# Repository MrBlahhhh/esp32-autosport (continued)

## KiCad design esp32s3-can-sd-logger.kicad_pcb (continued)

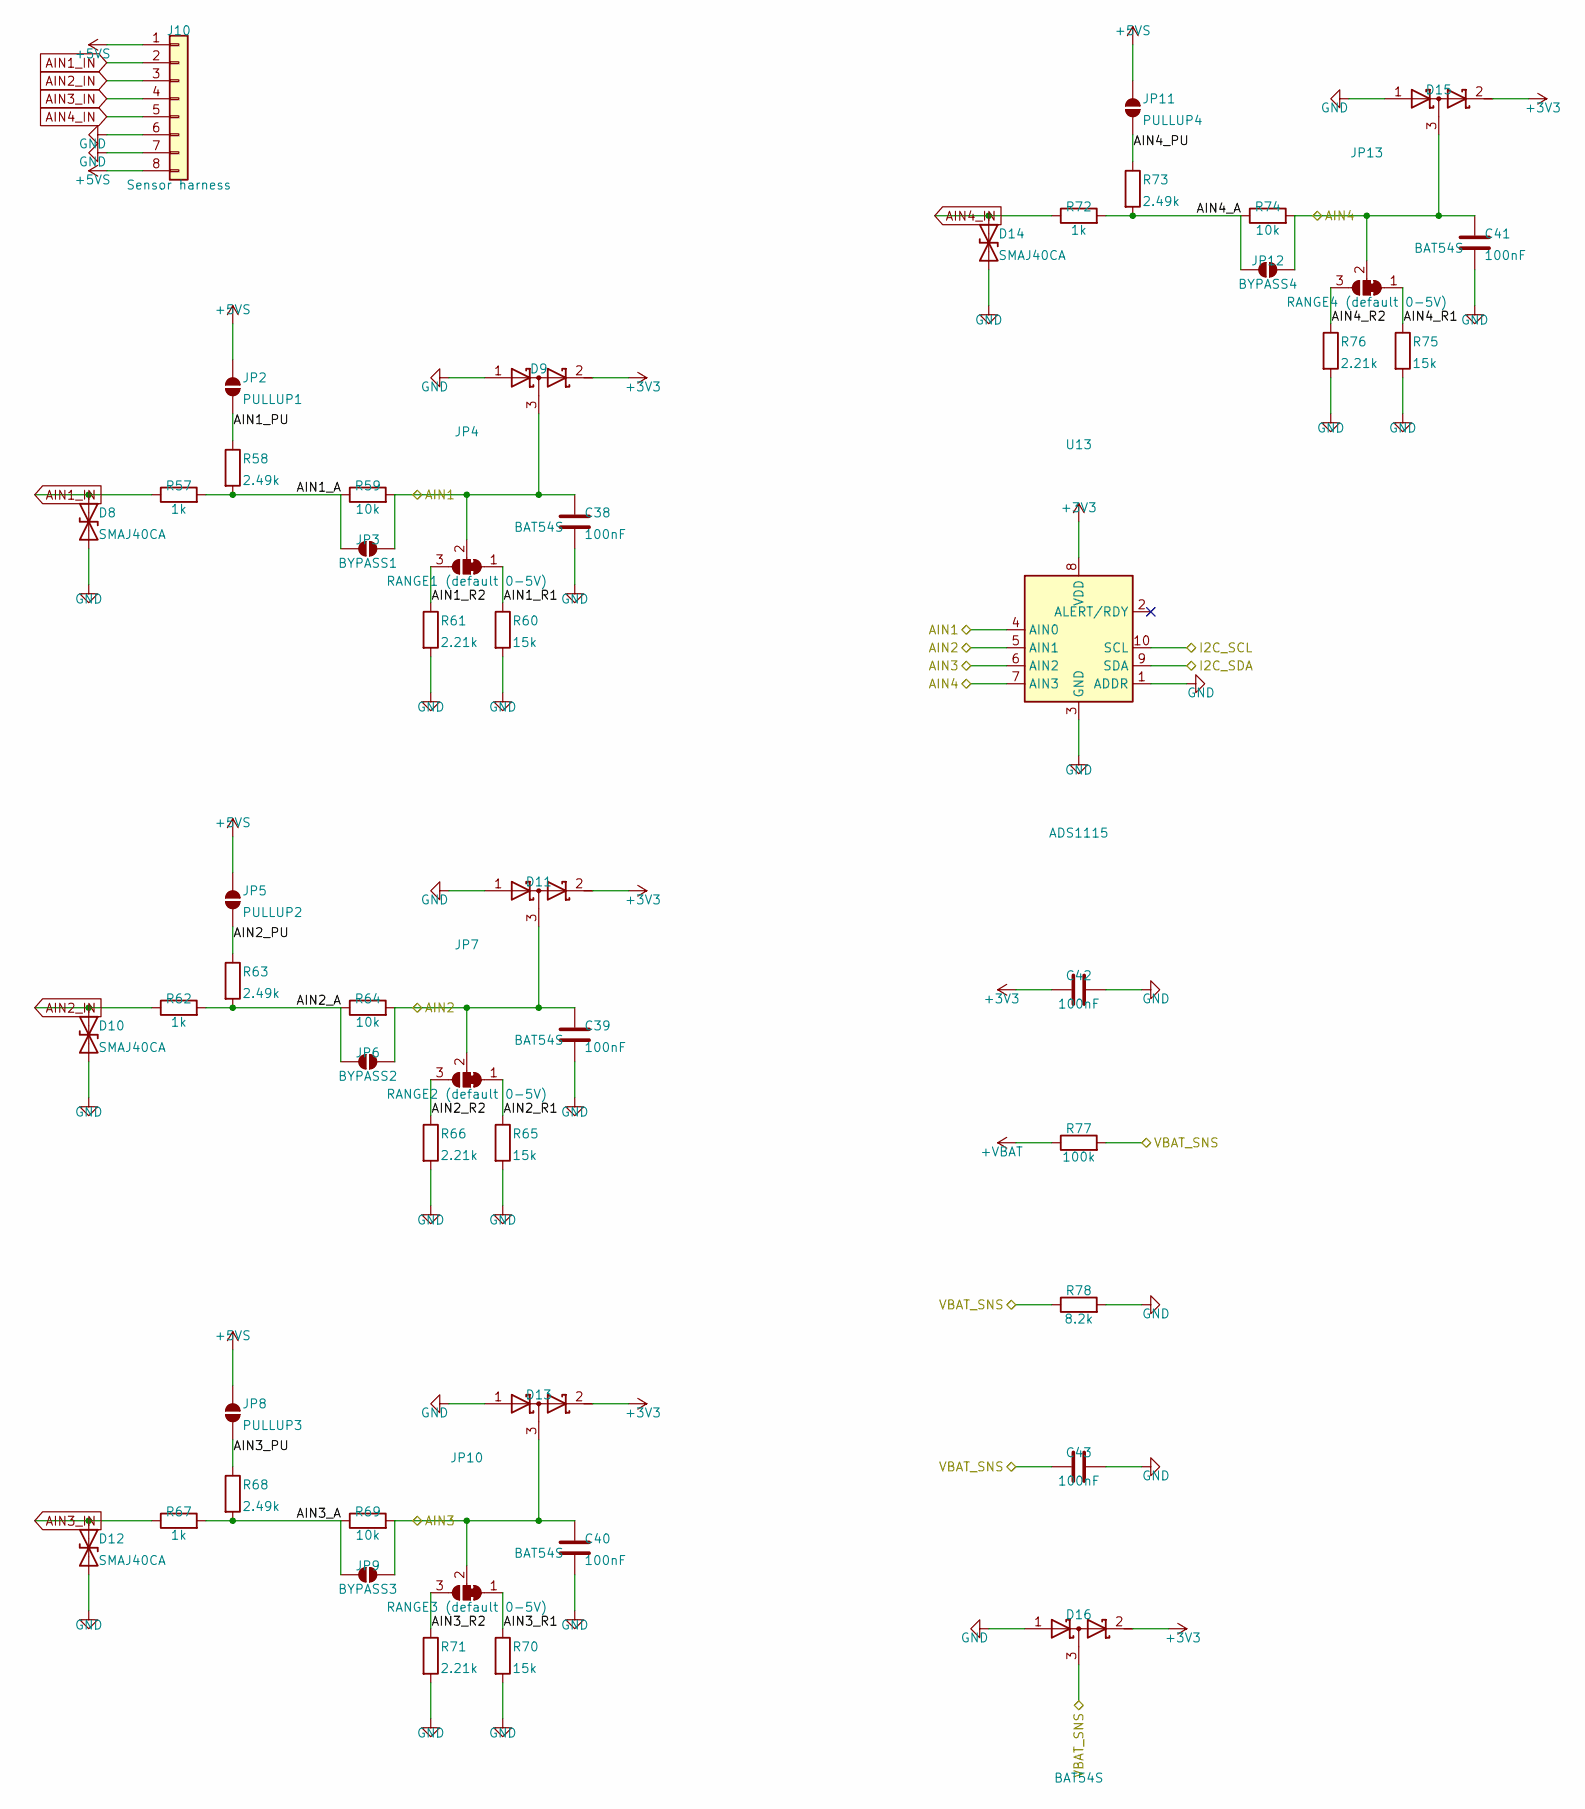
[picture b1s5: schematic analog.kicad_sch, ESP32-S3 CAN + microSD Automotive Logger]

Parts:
C38, C39, C40, C41, C42, C43: 100nF; C_0805_2012Metric; Voltage 16V
D8, D10, D12, D14: SMAJ40CA; D_SMA; MPN Littelfuse SMAJ40CA
D9, D11, D13, D15, D16: BAT54S; SOT-23; MPN MDD BAT54S
J10: Sensor harness; JST_PH_B8B-PH-K_1x08_P2.00mm_Vertical; MPN JST B8B-PH-K-S(LF)(SN)
JP2: PULLUP1; SolderJumper-2_P1.3mm_Open_Pad1.0x1.5mm
JP3: BYPASS1; SolderJumper-2_P1.3mm_Open_Pad1.0x1.5mm
JP4: RANGE1 (default 0-5V); SolderJumper-3_P1.3mm_Bridged12_Pad1.0x1.5mm
JP5: PULLUP2; SolderJumper-2_P1.3mm_Open_Pad1.0x1.5mm
JP6: BYPASS2; SolderJumper-2_P1.3mm_Open_Pad1.0x1.5mm
JP7: RANGE2 (default 0-5V); SolderJumper-3_P1.3mm_Bridged12_Pad1.0x1.5mm
JP8: PULLUP3; SolderJumper-2_P1.3mm_Open_Pad1.0x1.5mm
JP9: BYPASS3; SolderJumper-2_P1.3mm_Open_Pad1.0x1.5mm
JP10: RANGE3 (default 0-5V); SolderJumper-3_P1.3mm_Bridged12_Pad1.0x1.5mm
JP11: PULLUP4; SolderJumper-2_P1.3mm_Open_Pad1.0x1.5mm
JP12: BYPASS4; SolderJumper-2_P1.3mm_Open_Pad1.0x1.5mm
JP13: RANGE4 (default 0-5V); SolderJumper-3_P1.3mm_Bridged12_Pad1.0x1.5mm
R57, R62, R67, R72: 1k; R_0805_2012Metric; Tolerance 0.1%
R58, R63, R68, R73: 2.49k; R_0805_2012Metric
R59, R64, R69, R74: 10k; R_0805_2012Metric; Tolerance 0.1%
R60, R65, R70, R75: 15k; R_0805_2012Metric; Tolerance 0.1%
R61, R66, R71, R76: 2.21k; R_0805_2012Metric; Tolerance 0.1%
R77: 100k; R_0805_2012Metric
R78: 8.2k; R_0805_2012Metric
U13: ADS1115; VSSOP-10_3x3mm_P0.5mm; MPN ADS1115IDGSR

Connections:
+3V3: C42.1, D9.2 (K), D11.2 (K), D13.2 (K), D15.2 (K), D16.2 (K), U13.8 (VDD); also elsewhere on the board
+5VS: J10.1, J10.8, JP2.1 (A), JP5.1 (A), JP8.1 (A), JP11.1 (A); also elsewhere on the board
+VBAT: R77.1; also elsewhere on the board
AIN1: C38.1, D9.3 (common), JP3.2 (B), JP4.2 (C), R59.2, U13.4 (AIN0); also elsewhere on the board
AIN1_A: JP3.1 (A), R57.2, R58.2, R59.1
AIN1_IN: D8.1 (A1), J10.2, R57.1
AIN1_PU: JP2.2 (B), R58.1
AIN1_R1: JP4.1 (A), R60.1
AIN1_R2: JP4.3 (B), R61.1
AIN2: C39.1, D11.3 (common), JP6.2 (B), JP7.2 (C), R64.2, U13.5 (AIN1); also elsewhere on the board
AIN2_A: JP6.1 (A), R62.2, R63.2, R64.1
AIN2_IN: D10.1 (A1), J10.3, R62.1
AIN2_PU: JP5.2 (B), R63.1
AIN2_R1: JP7.1 (A), R65.1
AIN2_R2: JP7.3 (B), R66.1
AIN3: C40.1, D13.3 (common), JP9.2 (B), JP10.2 (C), R69.2, U13.6 (AIN2); also elsewhere on the board
AIN3_A: JP9.1 (A), R67.2, R68.2, R69.1
AIN3_IN: D12.1 (A1), J10.4, R67.1
AIN3_PU: JP8.2 (B), R68.1
AIN3_R1: JP10.1 (A), R70.1
AIN3_R2: JP10.3 (B), R71.1
AIN4: C41.1, D15.3 (common), JP12.2 (B), JP13.2 (C), R74.2, U13.7 (AIN3); also elsewhere on the board
AIN4_A: JP12.1 (A), R72.2, R73.2, R74.1
AIN4_IN: D14.1 (A1), J10.5, R72.1
AIN4_PU: JP11.2 (B), R73.1
AIN4_R1: JP13.1 (A), R75.1
AIN4_R2: JP13.3 (B), R76.1
I2C_SCL: U13.10 (SCL); also elsewhere on the board
I2C_SDA: U13.9 (SDA); also elsewhere on the board
VBAT_SNS: C43.1, D16.3 (common), R77.2, R78.1; also elsewhere on the board

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
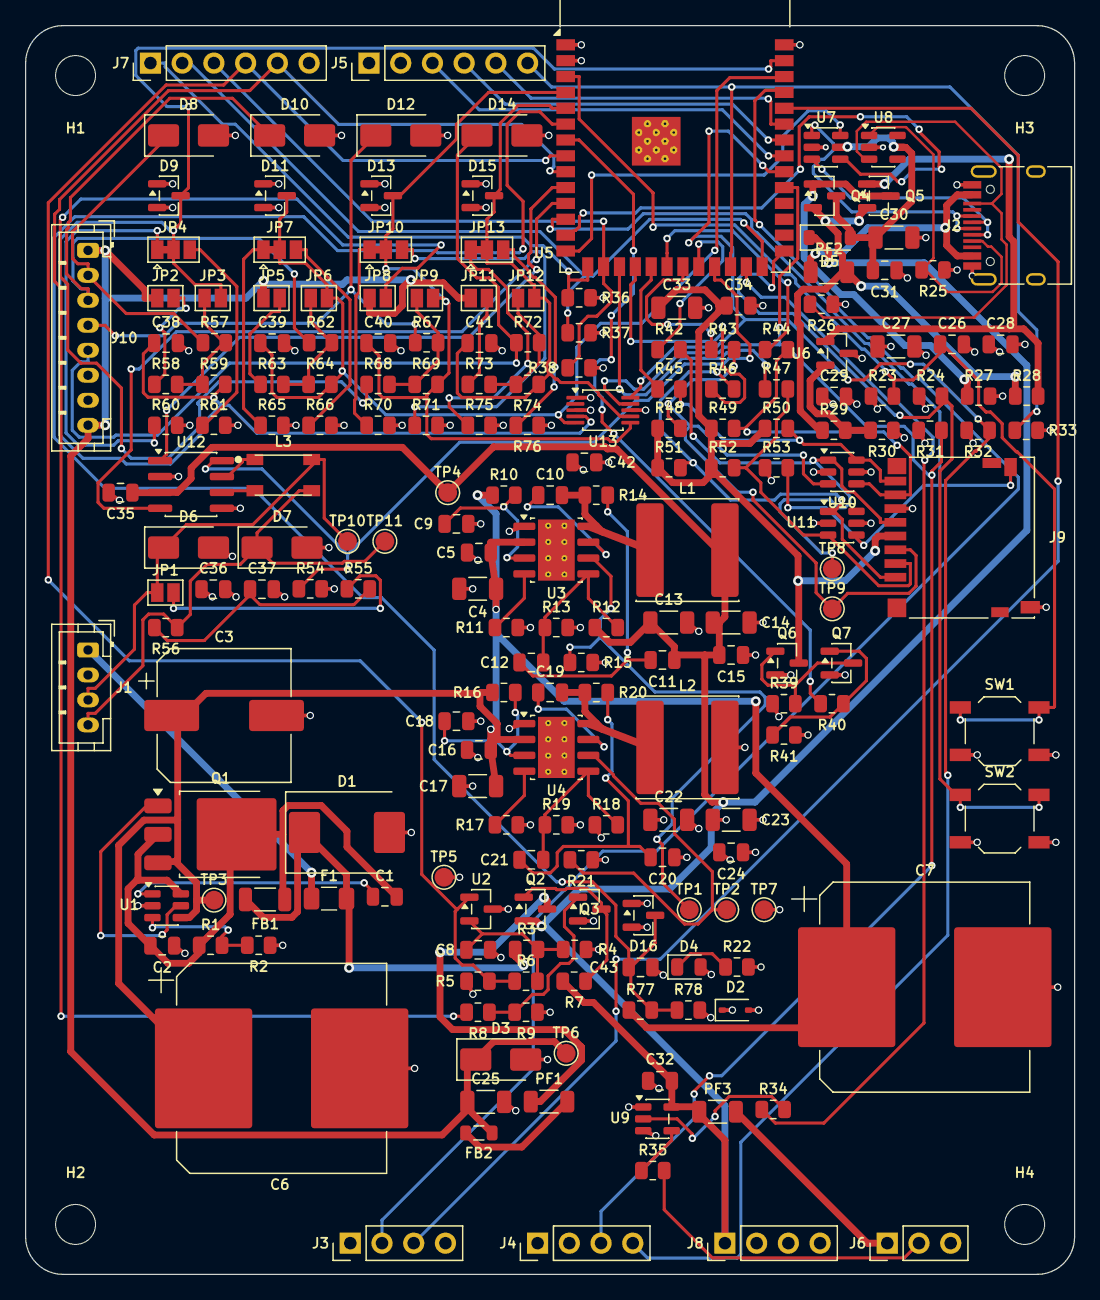
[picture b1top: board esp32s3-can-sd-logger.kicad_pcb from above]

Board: 4 copper layers, 84.0 x 100.0 mm, 206 parts (0 on the bottom side), 114 nets.

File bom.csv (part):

Qty (1 board),Qty (10 boards),References,Value,Voltage,Tolerance,Footprint,Manufacturer part number,LCSC,Notes
1,10,C1,1uF,50V,,Capacitor_SMD:C_0805_2012Metric,,,LM74700 charge-pump reservoir
4,40,C10 C11 C19 C20,2.2nF,50V,,Capacitor_SMD:C_0805_2012Metric,,,Bootstrap: datasheet mandates exactly 2.2nF X7R -- a larger value overstresses the internal VCC regulator and damages the device
2,20,C12 C21,270pF,50V,,Capacitor_SMD:C_0805_2012Metric,,,Ramp coupling capacitor CB
4,40,C13 C14 C22 C23,22uF,16V,,Capacitor_SMD:C_1206_3216Metric,,,
15,150,C15 C24 C28 C29 C31 C32 C34 C35 C36 C38 C39 C40 C41 C42 C43,100nF,16V,,Capacitor_SMD:C_0805_2012Metric,,,
3,30,C16 C2 C5,100nF,100V,,Capacitor_SMD:C_0805_2012Metric,,,LM74700 ANODE input capacitor: the datasheet requires a minimum 22nF at ANODE and this node is behind FB1 with nothing else on it
4,40,C25 C27 C30 C33,10uF,16V,,Capacitor_SMD:C_1206_3216Metric,,,
1,10,C26,1uF,16V,,Capacitor_SMD:C_0805_2012Metric,,,EN reset delay
1,10,C3,100uF,100V,,Capacitor_SMD:CP_Elec_10x10.5,Nichicon UCD2A101MNL1GS,,Bulk hold-up; any 100uF >=80V SMD electrolytic on a 10x10.5 land works -- match in the JLC catalog at order. Pin 1 is +
1,10,C37,4.7nF,50V,,Capacitor_SMD:C_0805_2012Metric,,,Split-termination common-mode stabiliser
2,20,C17 C4,10uF,100V,,Capacitor_SMD:C_1206_3216Metric,,,Switcher input bypass
2,20,C6 C7,330uF,100V,,Capacitor_SMD:CP_Elec_16x22,,,"Power-fail ride-through. With the sensor rail shed and the LEDs off the board draws about 0.35 W here, so the bank holds the rails up long enough to finish the block in flight and close the file. 16x22 rather than 16x17.5: the two footprints are identical in every copper and courtyard layer -- only the can is 4.5 mm taller -- so the extra 220 uF costs nothing but enclosure height. Any 330uF >=80V on a 16 mm land works; match in the JLC catalogue at order. Pin 1 is +"
1,10,C8,1nF,50V,,Capacitor_SMD:C_0805_2012Metric,,,Just enough to keep switching noise off the reference. Larger would delay the very detection this exists to make early
2,20,C18 C9,10nF,100V,,Capacitor_SMD:C_0805_2012Metric,,,EN sits on a bare 100k to VBAT; this keeps a high-impedance enable node quiet in a vehicle
1,10,D1,SMCJ40CA,,,Diode_SMD:D_SMC,Littelfuse SMCJ40CA,C80273,"40V standoff / 64.5V clamp @ 1500W, bidirectional: absorbs ISO 7637-2 pulse 5b load dump and the negative pulses, ahead of the FET. 40V not 33V so the part stands off the declared 36V input top"
1,10,D2,3.6V 300mW,,,Diode_SMD:D_SOD-323,onsemi MM3Z3V6T1G,C116949,Rail clamp: an analog input shorted to battery back-feeds ~1.6mA through its BAT54S into +3V3; with the MCU asleep the rail would otherwise float above the ESP32's 3.6V absolute maximum
1,10,D3,SMAJ6.0A,,,Diode_SMD:D_SMA,Littelfuse SMAJ6.0A,C223993,"Clamps harness-injected transients on the sensor 5V. 6.0V standoff, not 5.0V: a 5.0V part on a 5.0V rail leaks up to 800uA continuously"
1,10,D4,green,,,LED_SMD:LED_0805_2012Metric,,,"The board's only LED: +3V3 is up, so the whole supply chain came through -- battery, ideal diode, and both converters"
1,10,D5,40V 1A,,,Diode_SMD:D_SOD-123,PMEG4010,,"OR-ing: bench USB can power the board, but the 5V buck (5.00V) reverse-biases it whenever the car is connected"
2,20,D6 D7,SMAJ26CA,,,Diode_SMD:D_SMA,Diodes Inc SMAJ26CA-13-F,C134976,Bidirectional bus clamp
4,40,D10 D12 D14 D8,SMAJ40CA,,,Diode_SMD:D_SMA,Littelfuse SMAJ40CA,C223989,"Ch1 harness transient clamp (bidirectional, 400W)"
5,50,D11 D13 D15 D16 D9,BAT54S,,,Package_TO_SOT_SMD:SOT-23,MDD BAT54S,C408389,Ch1 rail clamp (both polarities)
1,10,F1,2A slow,,,Fuse:Fuse_1206_3216Metric,Littelfuse 0466002.NR,,"Sacrificial: only opens on a hard fault, not on reverse polarity"
1,10,FB1,600R,,,Inductor_SMD:L_1206_3216Metric,Wurth 742792625,,Conducted-emissions bead
1,10,FB2,600R,,,Inductor_SMD:L_0805_2012Metric,Wurth 742792022,,
4,40,H1 H2 H3 H4,M3,,,MountingHole:MountingHole_3.2mm_M3,,,
1,10,J1,PWR + CAN harness,,,Connector_JST:JST_PH_B4B-PH-K_1x04_P2.00mm_Vertical,JST B4B-PH-K-S(LF)(SN),C131334,"Pin 1 +12V, 2 GND, 3 CAN_H, 4 CAN_L (Autosport Labs harness order)"
1,10,J10,Sensor harness,,,Connector_JST:JST_PH_B8B-PH-K_1x08_P2.00mm_Vertical,JST B8B-PH-K-S(LF)(SN),C157974,Two 5V and two ground pins so sensors can be paired up
1,10,J2,USB-C,,,Connector_USB:USB_C_Receptacle_HRO_TYPE-C-31-M-12,HRO TYPE-C-31-M-12,C165948,Programming / CDC console only -- not a power path in the car
1,10,J3,UART0,,,Connector_PinHeader_2.54mm:PinHeader_1x04_P2.54mm_Vertical,,,
1,10,J4,I2C / Qwiic,,,Connector_PinHeader_2.54mm:PinHeader_1x04_P2.54mm_Vertical,,,
1,10,J5,SPI,,,Connector_PinHeader_2.54mm:PinHeader_1x06_P2.54mm_Vertical,,,IO40 SCK / IO41 MISO / IO42 MOSI / IO47 CS -- GPIO-matrix SPI
1,10,J6,WS2812,,,Connector_PinHeader_2.54mm:PinHeader_1x03_P2.54mm_Vertical,,,Shift-light header: +5V / 5V-logic DIN / GND
1,10,J7,Spare IO,,,Connector_PinHeader_2.54mm:PinHeader_1x06_P2.54mm_Vertical,,,"IO3/IO45/IO46 are strapping pins, each with a 10k pull-down -- anything attached must not fight them at boot. Pins 4 and 5 are no longer spare: IO15 is the power-fail interrupt and IO16 is the sensor-rail enable. They stay on the header as probe points, so the ride-through can be watched on a scope without unsoldering anything, but nothing else may drive them. The ground pin is here so a probe or a ribbon has a return"
1,10,J8,Rail break-out,,,Connector_PinHeader_2.54mm:PinHeader_1x04_P2.54mm_Vertical,,,
1,10,J9,microSD push-pull,,,Connector_Card:microSD_HC_Hirose_DM3D-SF,Hirose DM3D-SF,C719027,Push-pull socket; DET is the card-present switch
1,10,JP1,TERM (default OFF),,,Jumper:SolderJumper-2_P1.3mm_Open_Pad1.0x1.5mm,,,"Ships OPEN: unterminated. Bridge the pads only when this board is an END node on its own bus. A vehicle's bus -- OBD-II diagnostics included -- is already terminated at both ends, and a third 120 ohm across the pair takes it to about 40 ohm and can stop it working. Defaulting terminated made that an easy mistake to make"
1,10,JP10,RANGE3 (default 0-5V),,,Jumper:SolderJumper-3_P1.3mm_Bridged12_Pad1.0x1.5mm,,,"Ships BRIDGED 1-2 = the 0-5V range, which is what almost every automotive sensor is. Cut 1-2 and bridge 2-3 for 0-16V; cut 1-2 and leave both open for no divider (then close BYPASS3 for a raw 0-3.3V sensor). Defaulting to 0-5V also means the firmware's DIVIDER_GAIN matches the board as shipped"
1,10,JP11,PULLUP4,,,Jumper:SolderJumper-2_P1.3mm_Open_Pad1.0x1.5mm,,,Close for 2-wire NTC / open-collector sensors
1,10,JP12,BYPASS4,,,Jumper:SolderJumper-2_P1.3mm_Open_Pad1.0x1.5mm,,,Close for a raw 0-3.3V sensor (shorts the upper leg)
1,10,JP13,RANGE4 (default 0-5V),,,Jumper:SolderJumper-3_P1.3mm_Bridged12_Pad1.0x1.5mm,,,"Ships BRIDGED 1-2 = the 0-5V range, which is what almost every automotive sensor is. Cut 1-2 and bridge 2-3 for 0-16V; cut 1-2 and leave both open for no divider (then close BYPASS4 for a raw 0-3.3V sensor). Defaulting to 0-5V also means the firmware's DIVIDER_GAIN matches the board as shipped"
1,10,JP2,PULLUP1,,,Jumper:SolderJumper-2_P1.3mm_Open_Pad1.0x1.5mm,,,Close for 2-wire NTC / open-collector sensors
1,10,JP3,BYPASS1,,,Jumper:SolderJumper-2_P1.3mm_Open_Pad1.0x1.5mm,,,Close for a raw 0-3.3V sensor (shorts the upper leg)
1,10,JP4,RANGE1 (default 0-5V),,,Jumper:SolderJumper-3_P1.3mm_Bridged12_Pad1.0x1.5mm,,,"Ships BRIDGED 1-2 = the 0-5V range, which is what almost every automotive sensor is. Cut 1-2 and bridge 2-3 for 0-16V; cut 1-2 and leave both open for no divider (then close BYPASS1 for a raw 0-3.3V sensor). Defaulting to 0-5V also means the firmware's DIVIDER_GAIN matches the board as shipped"
1,10,JP5,PULLUP2,,,Jumper:SolderJumper-2_P1.3mm_Open_Pad1.0x1.5mm,,,Close for 2-wire NTC / open-collector sensors
1,10,JP6,BYPASS2,,,Jumper:SolderJumper-2_P1.3mm_Open_Pad1.0x1.5mm,,,Close for a raw 0-3.3V sensor (shorts the upper leg)
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
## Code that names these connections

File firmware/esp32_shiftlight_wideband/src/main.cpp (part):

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#define LED_TYPE    WS2812B
#define COLOR_ORDER GRB

#define CAN_TX_PIN  GPIO_NUM_17
#define CAN_RX_PIN  GPIO_NUM_18
#define CAN_S_PIN   21            // low = normal, high = listen-only

#define PWR_FAIL_PIN 15           // rising = harness below 11 V
#define SENS_EN_PIN  16           // high = +5VS live; off at reset
#define SD_PWR_EN_PIN 7
#define SD_CD_PIN     8
#define SD_CLK_PIN 14
#define SD_CMD_PIN 13
#define SD_D0_PIN  12
#define SD_D1_PIN  11
#define SD_D2_PIN  10
#define SD_D3_PIN   9

#define RPM_STALE_MS 2000         // blank the strip if CAN goes quiet

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// of the R53 board's 10k/10k, and using it here reads 17 % high all the way up
// the range. gen/simulate_firmware.py study 3 measures it end to end.
static const float DIVIDER_GAIN = 1.7334f;
static const int   ESP_ADC_PIN  = 1;       // AIN1 = GPIO1 = ADC1_CH0
static const int   VBAT_ADC_PIN = 6;       // VBAT_SNS = GPIO6, divided by 11
static const float VBAT_DIVIDER = 11.0f;

// I2C is on the Qwiic header, not the pins the R53 board used — GPIO7 and
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
void IRAM_ATTR onPowerFail() {
  powerFailed = true;
  digitalWrite(SENS_EN_PIN, LOW);
}

/**
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  // CAN_S low = normal mode. R40 already pulls it there so the transceiver is
  // sane while the MCU is in reset; drive it anyway so the state is the
  // firmware's decision and not a resistor's.
  pinMode(CAN_S_PIN, OUTPUT);
  digitalWrite(CAN_S_PIN, LOW);

  twai_general_config_t g =
      TWAI_GENERAL_CONFIG_DEFAULT(CAN_TX_PIN, CAN_RX_PIN, TWAI_MODE_NORMAL);
  g.rx_queue_len = 32;   // FastLED.show() blocks ~0.5 ms; don't drop frames in it
  twai_timing_config_t t = TWAI_TIMING_CONFIG_500KBITS();
  twai_filter_config_t f = TWAI_FILTER_CONFIG_ACCEPT_ALL();
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
// --- microSD -----------------------------------------------------------------
void sdInit() {
  pinMode(SD_CD_PIN, INPUT);
  pinMode(SD_PWR_EN_PIN, OUTPUT);
  digitalWrite(SD_PWR_EN_PIN, HIGH);       // the card supply is switched
  delay(10);                               // let the rail come up before clocking

  SD_MMC.setPins(SD_CLK_PIN, SD_CMD_PIN, SD_D0_PIN, SD_D1_PIN, SD_D2_PIN, SD_D3_PIN);
  if (!SD_MMC.begin("/sdcard", false)) {   // 4-bit: ~4x the write throughput
    Serial.println("SD: mount failed");
    return;
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
/**
 * The firmware half of README section 2. The hardware guarantees roughly
 * 108 ms between PWR_FAIL and the converters dropping out; this is what spends
 * it. Order matters: the sensor rail is already off (the ISR did it), the strip
 * goes dark so it is not drawing from the bank, then the file is closed, and
 * only then is the card supply removed — with SD_MMC.end() first, because
 * dropping SD_PWR_EN while the bus pins are still driven back-feeds the card
 * through its ESD structures (README section 5).
 */
void shutdown() {
  if (shuttingDown) return;
  shuttingDown = true;
  digitalWrite(SENS_EN_PIN, LOW);          // idempotent; the ISR got here first

  FastLED.clear(true);

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    SD_MMC.end();
    sdUp = false;
  }
  digitalWrite(SD_PWR_EN_PIN, LOW);

  Serial.printf("PWR_FAIL at %lu ms: %lu lines flushed and closed\n", millis(), logLines);
}
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  // +5VS is off at reset by design: it is an external load firmware must be
  // able to shed. Nothing on the sensor harness reads anything until this
  // goes high, and every analog reading before it is a zero.
  pinMode(SENS_EN_PIN, OUTPUT);
  digitalWrite(SENS_EN_PIN, HIGH);

  // Armed before anything slow runs. An ignition cut during BLE bring-up is
  // still an ignition cut, and the card is not open yet but the interrupt
  // still has to be the thing that shuts the rail down.
  pinMode(PWR_FAIL_PIN, INPUT);
  attachInterrupt(digitalPinToInterrupt(PWR_FAIL_PIN), onPowerFail, RISING);

  // BLE goes first, on purpose. The BT controller wants a sizeable block of
  // internal RAM (it cannot use PSRAM) and it is the one subsystem here that
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
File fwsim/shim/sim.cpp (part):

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    fault(SEV_ERROR, "PIN_PSRAM", "GPIO%d driven, but it is octal PSRAM on this module", gpio);
  if (p && p->role == ROLE_SD_PWR_EN && level == 0 && s.sd_begun)
    fault(SEV_WARN, "SD_BACKFEED",
          "SD_PWR_EN (GPIO%d) dropped while the card is still mounted. Call SD_MMC.end() first, "
          "or the MCU keeps driving the bus into an unpowered card through its ESD structures "
          "(README section 5)",
          gpio);
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    int en = gpio_with_role(ROLE_SENS_EN);
    fault(SEV_ERROR, "SENSOR_RAIL_OFF",
          "channel %d (GPIO%d) is excited from +5VS, which is off at reset -- firmware never drove "
          "SENS_EN (GPIO%d) high, so this channel reads 0 V no matter what the sensor does",
          ch, gpio, en);
    src = 0.0;
  }
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  s.can_pins_ok = true;
  if (want_tx >= 0 && tx != want_tx) {
    const PinDef* p = find_pin(tx);
    fault(SEV_ERROR, "CAN_TX_PIN",
          "TWAI TX assigned to GPIO%d (%s), but this board wires the transceiver TXD to GPIO%d -- "
          "no frames will ever arrive, and GPIO%d is now driven by the CAN controller",
          tx, p ? role_name(p->role) : "not connected", want_tx, tx);
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  }
  if (want_rx >= 0 && rx != want_rx) {
    const PinDef* p = find_pin(rx);
    fault(SEV_ERROR, "CAN_RX_PIN",
          "TWAI RX assigned to GPIO%d (%s), but this board wires the transceiver RXD to GPIO%d",
          rx, p ? role_name(p->role) : "not connected", want_rx, rx);
    s.can_pins_ok = false;
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  int cs = gpio_with_role(ROLE_CAN_S);
  if (cs >= 0 && !pin_driven(cs))
    fault(SEV_NOTE, "CAN_S_DEFAULT",
          "CAN_S (GPIO%d) left undriven; R54 pulls it low so the transceiver comes up in normal "
          "mode. Drive it high for listen-only if this node must never ACK",
          cs);
}
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  s.i2c_pins_ok = true;
  if (want_sda >= 0 && sda != want_sda) {
    const PinDef* p = find_pin(sda);
    fault(SEV_ERROR, "I2C_SDA_PIN",
          "I2C SDA brought up on GPIO%d, but on this board GPIO%d is %s (%s) and the bus is on "
          "GPIO%d. Driving it toggles that function",
          sda, sda, p ? p->net : "nothing", p ? role_name(p->role) : "not connected", want_sda);
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  }
  if (want_scl >= 0 && scl != want_scl) {
    const PinDef* p = find_pin(scl);
    fault(SEV_ERROR, "I2C_SCL_PIN",
          "I2C SCL brought up on GPIO%d, but on this board GPIO%d is %s (%s) and the bus is on "
          "GPIO%d",
          scl, scl, p ? p->net : "nothing", p ? role_name(p->role) : "not connected", want_scl);
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  int pwr = gpio_with_role(ROLE_SD_PWR_EN);
  if (pwr >= 0 && !(s.level.count(pwr) && s.level[pwr] == 1)) {
    fault(SEV_ERROR, "SD_UNPOWERED",
          "SD_MMC.begin() with SD_PWR_EN (GPIO%d) low -- the card supply is switched through "
          "Q2/Q3 and off at reset, so there is no card on the bus to answer",
          pwr);
    return false;
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  s.stop_reason = why ? why : "";
  if (s.pwr_fail_at_ms >= 0.0 && !s.pwr_fail_observed)
    fault(SEV_ERROR, "PWR_FAIL_IGNORED",
          "PWR_FAIL (GPIO%d) asserted at %.1f ms and firmware never read it or attached an "
          "interrupt to it. The hardware buys a %.0f ms window to shed the sensor rail and close "
          "the file; nothing in this firmware spends it",
          gpio_with_role(ROLE_PWR_FAIL), s.pwr_fail_at_ms, board().ridethru_shed_ms);
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
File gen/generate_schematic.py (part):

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
part(pw, "J", "Connector_Generic:Conn_01x04", "PWR + CAN harness", JST4,
     {"1": "VBAT_IN", "2": "GND", "3": "CAN_H", "4": "CAN_L"},
     "JST B4B-PH-K-S(LF)(SN)", "Pin 1 +12V, 2 GND, 3 CAN_H, 4 CAN_L "
     "(Autosport Labs harness order)", lcsc="C131334")
part(pw, "F", "Device:Fuse", "2A slow", "Fuse:Fuse_1206_3216Metric",
     {"1": "VBAT_IN", "2": "VBAT_F"}, "Littelfuse 0466002.NR",
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     {"1": "SENS_EN_G", "2": "GND", "3": "SENS_G"}, "onsemi 2N7002",
     "Level shifter: the P-FET's gate has to be pulled to GND from 5V, and "
     "a 3.3V GPIO cannot do that directly", lcsc="C8545")
R(pw, "10k", "SENS_EN", "SENS_EN_G", note="GPIO series/gate resistor")
R(pw, "100k", "SENS_EN_G", "GND",
  note="Holds the level shifter off while the MCU is in reset")

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     {"1": "VSENS_SW", "2": "VSENS_F"}, "Bourns MF-MSMF020",
     "Resettable: a shorted sensor wire trips this, not the board. Now behind "
     "the load switch, so a short is also something firmware can clear by "
     "dropping SENS_EN, rather than waiting for the fuse to cool",
     lcsc="C719178")
part(pw, "FB", "Device:L", "600R", "Inductor_SMD:L_0805_2012Metric",
     {"1": "VSENS_F", "2": "+5VS"}, "Wurth 742792022")
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            # Owning the net means the block's wires reach every pin on it --
            # not merely that every part is a member. The microSD connector
            # belongs to the SD block, but its VDD pin is fanned out to a
            # label like its eight neighbours, so SD_VDD is still a name the
            # sheet shares and has to be written as a global.
            elsewhere = {(p["ref"], num) for s2 in SHEETS for p in s2["parts"]
                         for num, v in p["pins"].items()
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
